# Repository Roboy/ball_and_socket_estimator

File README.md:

# Neural network ball socket estimator

## Install

* Pytorch `conda install pytorch torchvision torchaudio cudatoolkit=10.2 -c pytorch`

* `pip install -r requirements.txt`

## Data collection

Switch to `python` folder as your working directory `cd python`

* Generate data using `python particle_swarm.py --body_part BODY_PART`
  
 with `BODY_PART = {head, shoulder_left, shoulder_right, hand_left, hand_right}`

* Topics to record:

    - `/roboy/pinky/sensing/external_joint_states`
    - `/roboy/pinky/middleware/MagneticSensor`
    - `/tracking_loss`
    - `/roboy/pinky/control/cardsflow_joint_states`
    - `/roboy/pinky/simulation/joint_targets`

## Training

* Convert `bags` to `csv` using `write_dataset_from_bag.ipynb`

* Run `data_analysis.ipynb` to make sure all the inputs and outputs are correct

* Train an LSTM network using `training.ipynb`

## Prediction
`cd python`
* Run the trained network `python predict_lstm.py`

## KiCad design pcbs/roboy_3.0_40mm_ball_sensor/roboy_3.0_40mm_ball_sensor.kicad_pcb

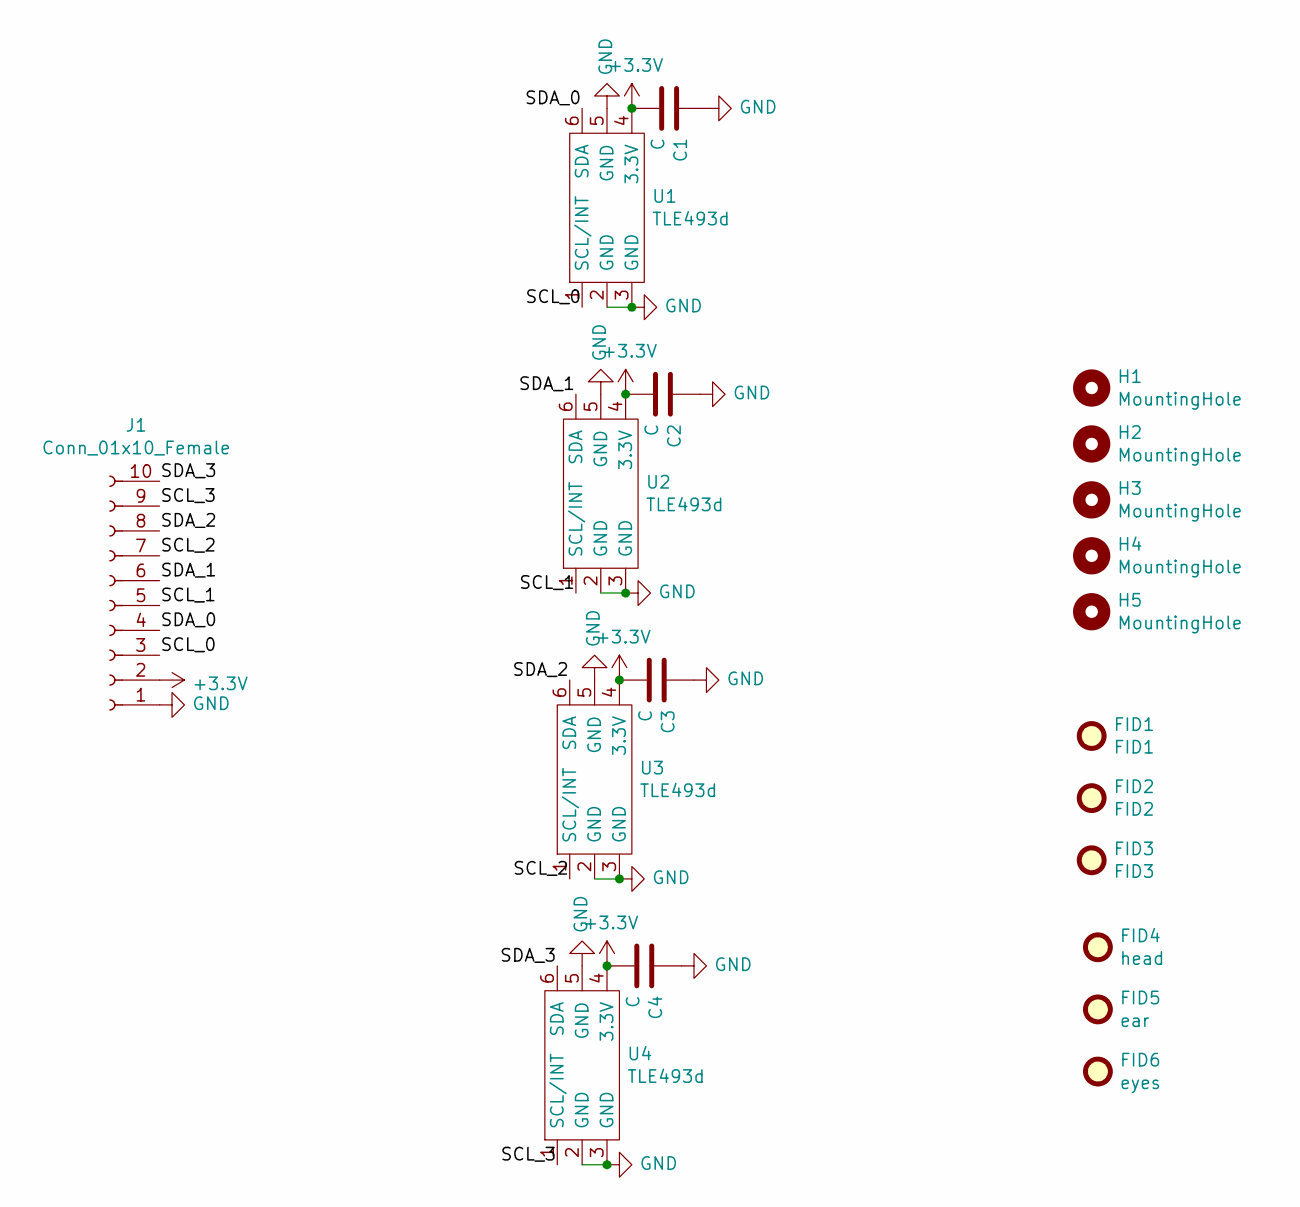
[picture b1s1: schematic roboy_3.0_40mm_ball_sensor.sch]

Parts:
C1, C2, C3, C4: C; C_0402_1005Metric
FID1: FID1; Fiducial_0.5mm_Mask1mm
FID2: FID2; Fiducial_0.5mm_Mask1mm
FID3: FID3; Fiducial_0.5mm_Mask1mm
FID4: head; R1_face_mask_5.5mm
FID5: ear; R1_ear_silk_5.5mm
FID6: eyes; R1_eyes_mask_5.5mm
H1, H2, H3, H4, H5: MountingHole; MountingHole_3.2mm_M3
J1: Conn_01x10_Female; TE-Connectivity_Micro-Match_connector_02x05_Pitch_1.27mm
U1, U2, U3, U4: TLE493d

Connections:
+3V3: C1.2, C2.2, C3.2, C4.2, J1.2, U1.4 (3.3V), U2.4 (3.3V), U3.4 (3.3V), U4.4 (3.3V)
/SCL_0: J1.3, U1.1 (SCL/INT)
/SCL_1: J1.5, U2.1 (SCL/INT)
/SCL_2: J1.7, U3.1 (SCL/INT)
/SCL_3: J1.9, U4.1 (SCL/INT)
/SDA_0: J1.4, U1.6 (SDA)
/SDA_1: J1.6, U2.6 (SDA)
/SDA_2: J1.8, U3.6 (SDA)
/SDA_3: J1.10, U4.6 (SDA)
GND: C1.1, C2.1, C3.1, C4.1, J1.1, U1.2 (GND), U1.3 (GND), U1.5 (GND), U2.2 (GND), U2.3 (GND), U2.5 (GND), U3.2 (GND), U3.3 (GND), U3.5 (GND), U4.2 (GND), U4.3 (GND), U4.5 (GND)

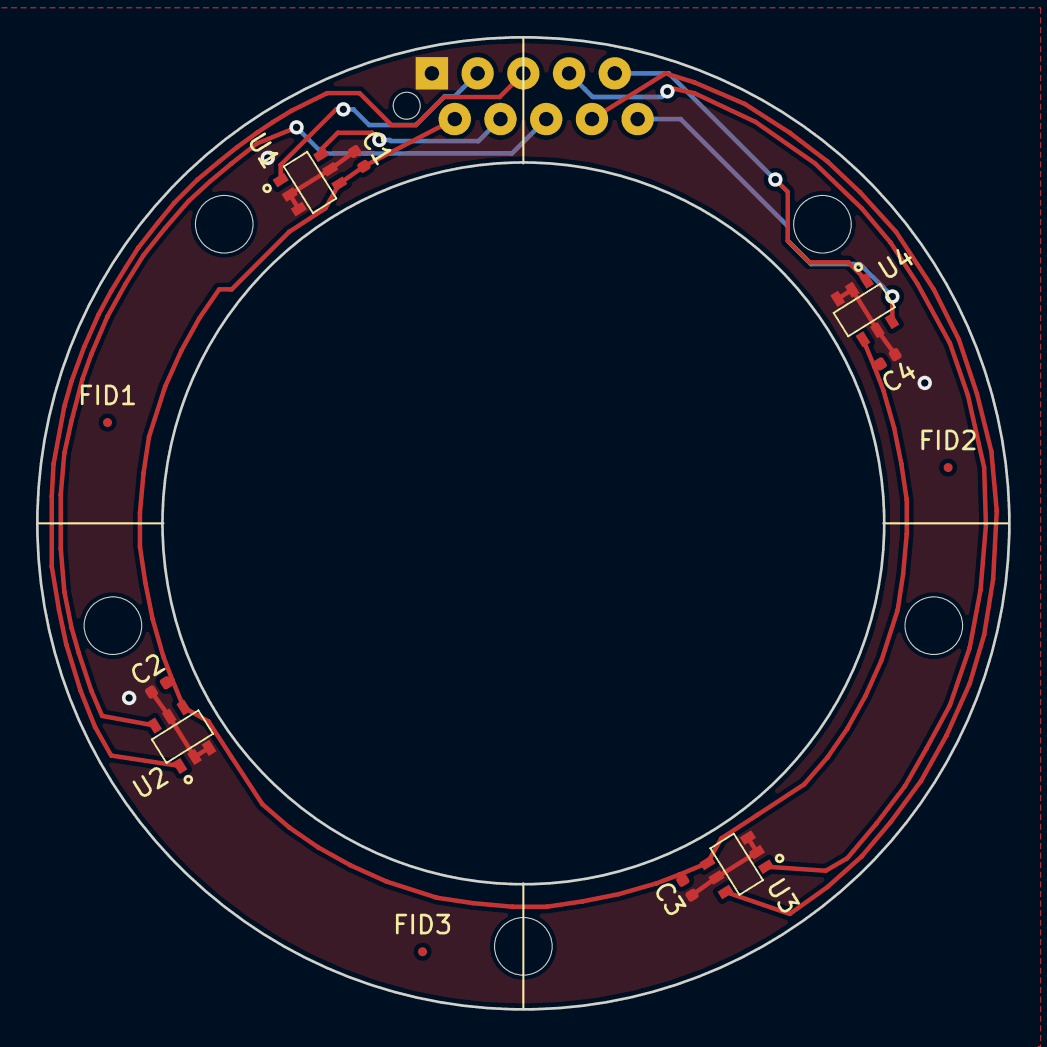
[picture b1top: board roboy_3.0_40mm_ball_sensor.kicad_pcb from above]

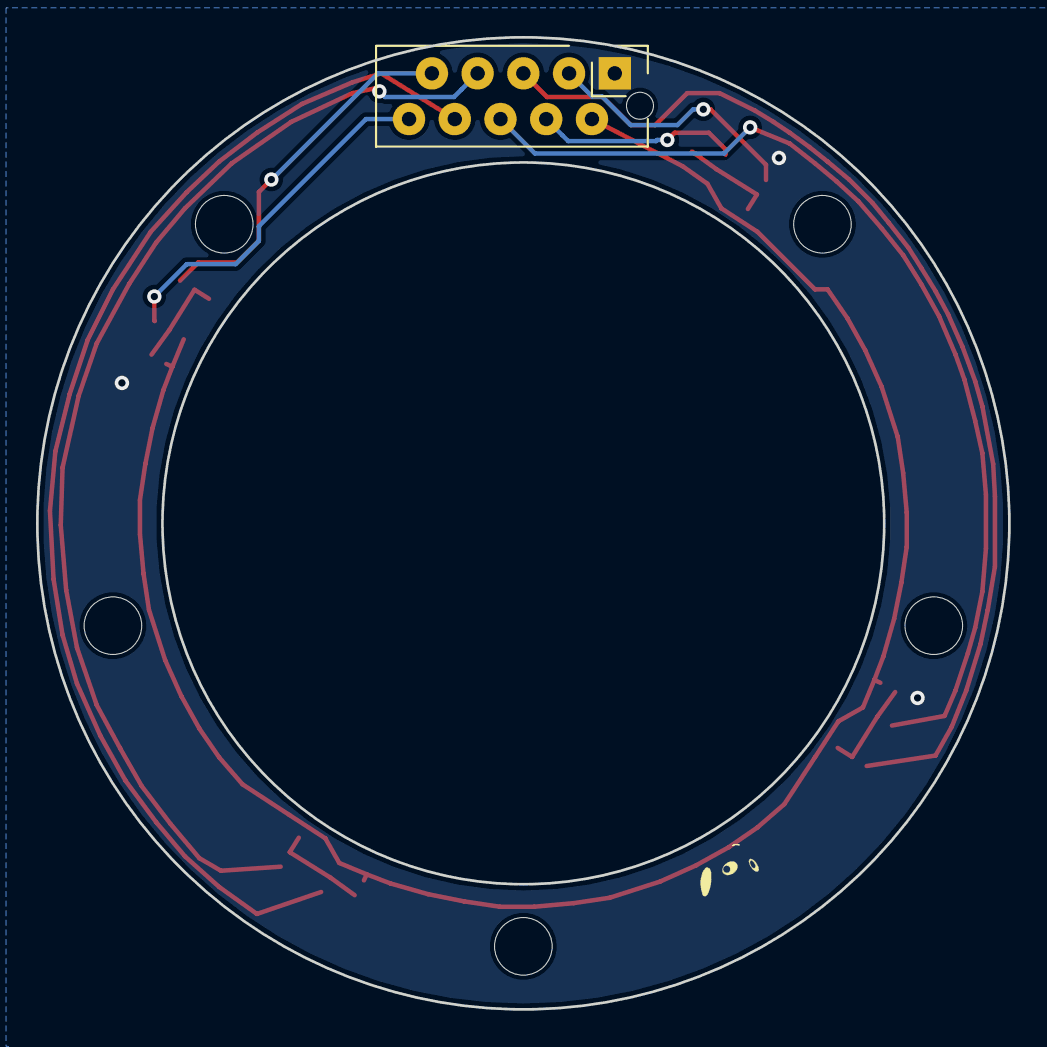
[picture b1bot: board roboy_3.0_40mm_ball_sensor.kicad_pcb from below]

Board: 2 copper layers, 54.0 x 54.0 mm, 20 parts (4 on the bottom side), 10 nets.

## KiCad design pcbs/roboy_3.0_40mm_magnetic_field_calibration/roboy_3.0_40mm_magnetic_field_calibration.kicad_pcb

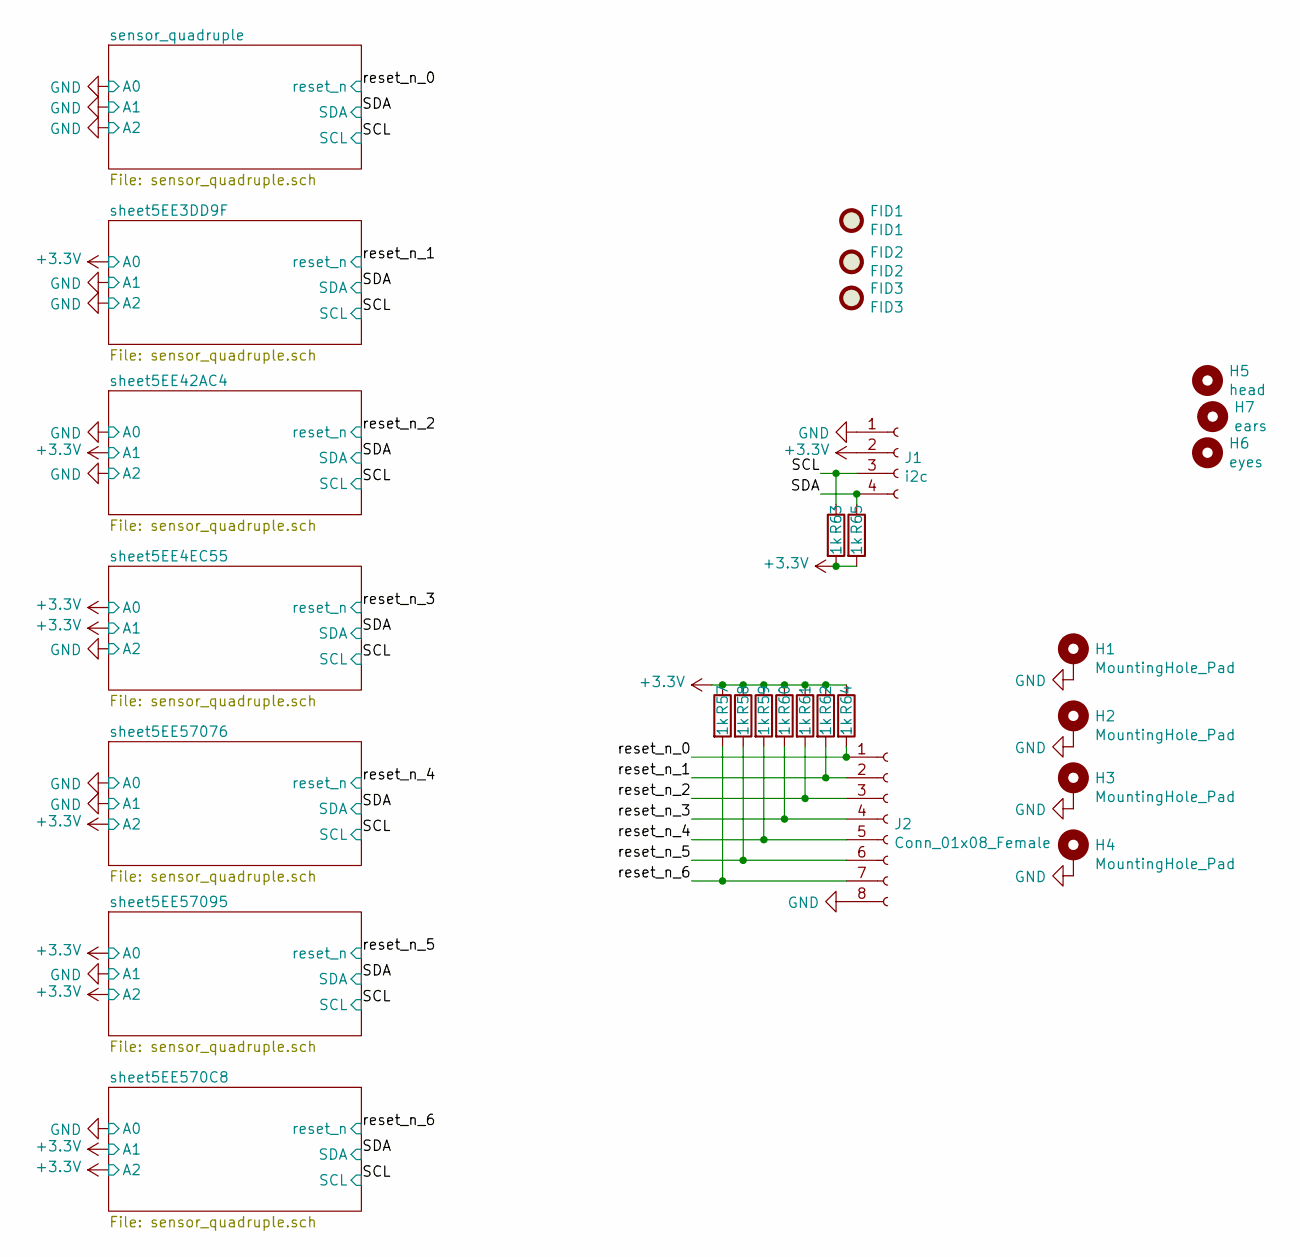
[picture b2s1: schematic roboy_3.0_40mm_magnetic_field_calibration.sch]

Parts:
FID1: FID1; Fiducial_0.75mm_Mask1.5mm
FID2: FID2; Fiducial_0.75mm_Mask1.5mm
FID3: FID3; Fiducial_0.75mm_Mask1.5mm
H1, H2, H3, H4: MountingHole_Pad; MountingHole_3mm_Pad
H5: head; R1_face_mask_5.5mm
H6: eyes; R1_eyes_mask_5.5mm
H7: ears; R1_ear_silk_5.5mm
J1: i2c; TE-Connectivity_Micro-Match_connector_02x02_Pitch_1.27mm
J2: Conn_01x08_Female; micro_match_female_8pos_SMT
R57, R58, R59, R60, R61, R62, R63, R64, R65: 1k; R_0402_1005Metric

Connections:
+3V3: J1.2, R57.1, R58.1, R59.1, R60.1, R61.1, R62.1, R63.2, R64.1, R65.2; also elsewhere on the board
/SCL: J1.3, R63.1; also elsewhere on the board
/SDA: J1.4, R65.1; also elsewhere on the board
/reset_n_0: J2.1, R64.2; also elsewhere on the board
/reset_n_1: J2.2, R62.2; also elsewhere on the board
/reset_n_2: J2.3, R61.2; also elsewhere on the board
/reset_n_3: J2.4, R60.2; also elsewhere on the board
/reset_n_4: J2.5, R59.2; also elsewhere on the board
/reset_n_5: J2.6, R58.2; also elsewhere on the board
/reset_n_6: J2.7, R57.2; also elsewhere on the board
GND: H1.1, H2.1, H3.1, H4.1, J1.1, J2.8; also elsewhere on the board

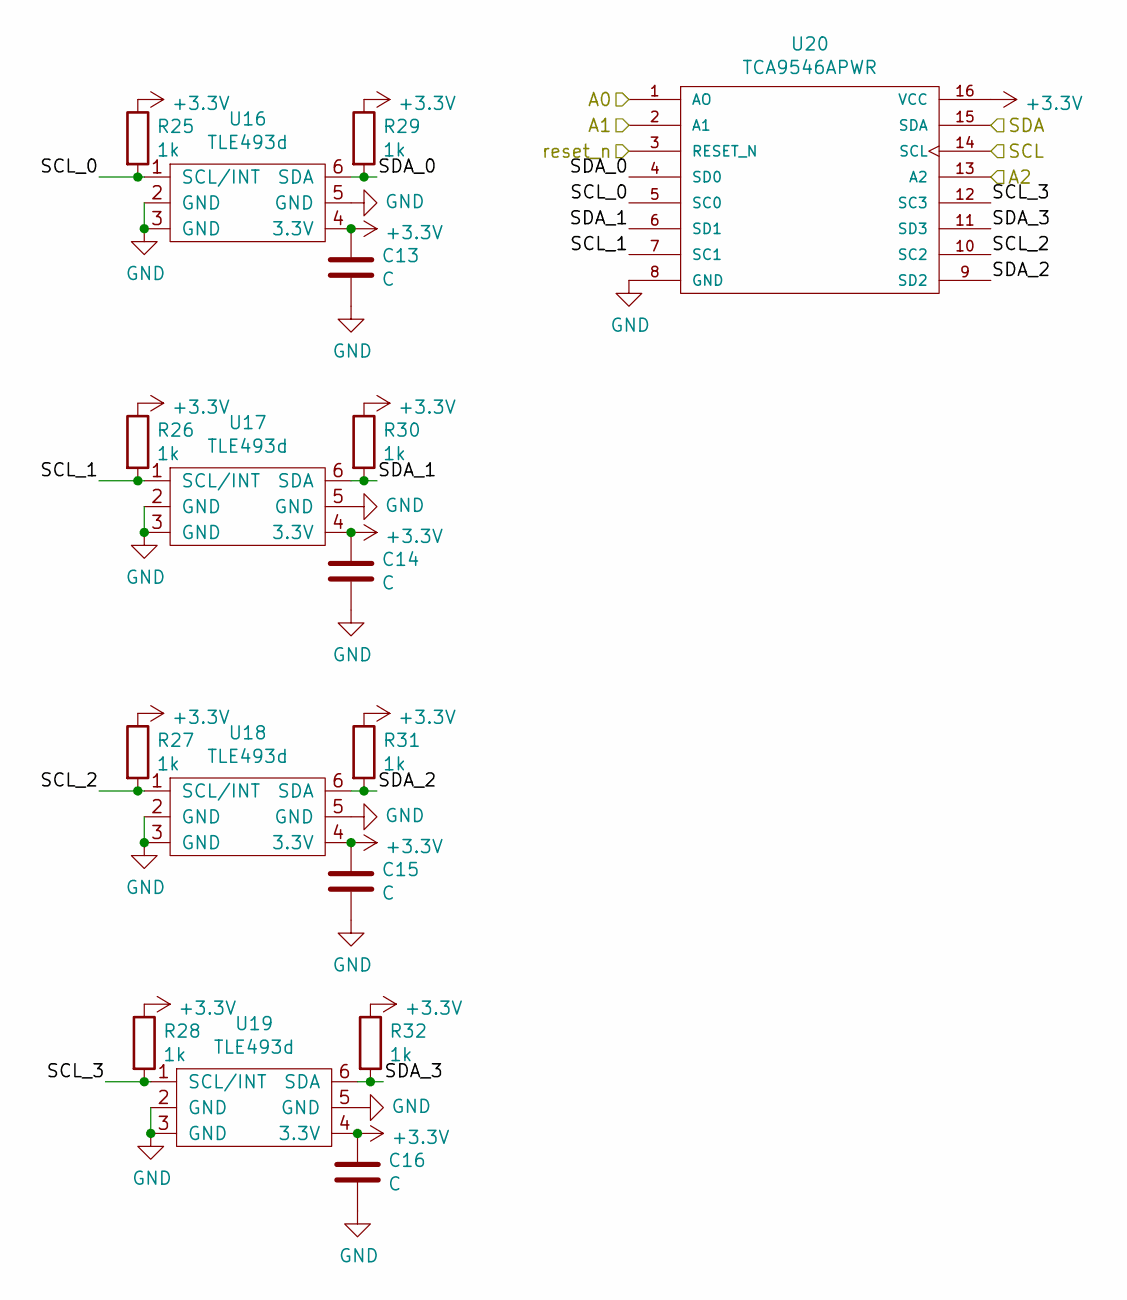
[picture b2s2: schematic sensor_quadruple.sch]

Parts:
C1, C2, C3, C4: C; C_0402_1005Metric
R1, R2, R3, R4, R5, R6, R7, R8: 1k; R_0402_1005Metric
U1, U2, U3, U4: TLE493d
U5: TCA9546APWR; SOP65P640X120-16N

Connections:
+3V3: C1.1, C2.1, C3.1, C4.1, R1.1, R2.1, R3.1, R4.1, R5.1, R6.1, R7.1, R8.1, U1.4 (3.3V), U2.4 (3.3V), U3.4 (3.3V), U4.4 (3.3V), U5.16 (VCC); also elsewhere on the board
/SCL: U5.14 (SCL); also elsewhere on the board
/SDA: U5.15 (SDA); also elsewhere on the board
/reset_n_0: U5.3 (RESET_N); also elsewhere on the board
/sensor_quadruple/SCL_0: R1.2, U1.1 (SCL/INT), U5.5 (SC0)
/sensor_quadruple/SCL_1: R2.2, U2.1 (SCL/INT), U5.7 (SC1)
/sensor_quadruple/SCL_2: R3.2, U3.1 (SCL/INT), U5.10 (SC2)
/sensor_quadruple/SCL_3: R4.2, U4.1 (SCL/INT), U5.12 (SC3)
/sensor_quadruple/SDA_0: R5.2, U1.6 (SDA), U5.4 (SD0)
/sensor_quadruple/SDA_1: R6.2, U2.6 (SDA), U5.6 (SD1)
/sensor_quadruple/SDA_2: R7.2, U3.6 (SDA), U5.9 (SD2)
/sensor_quadruple/SDA_3: R8.2, U4.6 (SDA), U5.11 (SD3)
GND: C1.2, C2.2, C3.2, C4.2, U1.2 (GND), U1.3 (GND), U1.5 (GND), U2.2 (GND), U2.3 (GND), U2.5 (GND), U3.2 (GND), U3.3 (GND), U3.5 (GND), U4.2 (GND), U4.3 (GND), U4.5 (GND), U5.1 (AO), U5.2 (A1), U5.8 (GND), U5.13 (A2); also elsewhere on the board

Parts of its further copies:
C5, C6, C7, C8, C9, C10, C11, C12, C13, C14, C15, C16, C17, C18, C19, C20, C21, C22, C23, C24, C25, C26, C27, C28: C; C_0402_1005Metric
R9, R10, R11, R12, R13, R14, R15, R16, R17, R18, R19, R20, R21, R22, R23, R24, R25, R26, R27, R28, R29, R30, R31, R32, R33, R34, R35, R36, R37, R38, R39, R40, R41, R42, R43, R44, R45, R46, R47, R48, R49, R50, R51, R52, R53, R54, R55, R56: 1k; R_0402_1005Metric
U6, U7, U8, U9, U11, U12, U13, U14, U16, U17, U18, U19, U21, U22, U23, U24, U26, U27, U28, U29, U31, U32, U33, U34: TLE493d
U10, U15, U20, U25, U30, U35: TCA9546APWR; SOP65P640X120-16N

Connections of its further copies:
+3V3: C5.1, C6.1, C7.1, C8.1, C9.1, C10.1, C11.1, C12.1, C13.1, C14.1, C17.1, C18.1, C19.1, C20.1, C21.1, C22.1, C23.1, C24.1, C25.1, C26.1, C27.1, C28.1, R9.1, R10.1, R11.1, R12.1, R13.1, R14.1, R15.1, R16.1, R17.1, R18.1, R19.1, R20.1, R21.1, R22.1, R23.1, R24.1, R25.1, R26.1, R29.1, R30.1, R33.1, R34.1, R35.1, R36.1, R37.1, R38.1, R39.1, R40.1, R41.1, R42.1, R43.1, R44.1, R45.1, R46.1, R47.1, R48.1, R49.1, R50.1, R51.1, R52.1, R53.1, R54.1, R55.1, R56.1, U6.4 (3.3V), U7.4 (3.3V), U8.4 (3.3V), U9.4 (3.3V), U10.1 (AO), U10.16 (VCC), U11.4 (3.3V), U12.4 (3.3V), U13.4 (3.3V), U14.4 (3.3V), U15.2 (A1), U15.16 (VCC), U16.4 (3.3V), U17.4 (3.3V), U20.1 (AO), U20.2 (A1), U20.16 (VCC), U21.4 (3.3V), U22.4 (3.3V), U23.4 (3.3V), U24.4 (3.3V), U25.13 (A2), U25.16 (VCC), U26.4 (3.3V), U27.4 (3.3V), U28.4 (3.3V), U29.4 (3.3V), U30.1 (AO), U30.13 (A2), U30.16 (VCC), U31.4 (3.3V), U32.4 (3.3V), U33.4 (3.3V), U34.4 (3.3V), U35.2 (A1), U35.13 (A2), U35.16 (VCC); also elsewhere on the board
/SCL: U10.14 (SCL), U15.14 (SCL), U20.14 (SCL), U25.14 (SCL), U30.14 (SCL), U35.14 (SCL); also elsewhere on the board
/SDA: U10.15 (SDA), U15.15 (SDA), U20.15 (SDA), U25.15 (SDA), U30.15 (SDA), U35.15 (SDA); also elsewhere on the board
/reset_n_1: U10.3 (RESET_N); also elsewhere on the board
/reset_n_2: U15.3 (RESET_N); also elsewhere on the board
/reset_n_3: U20.3 (RESET_N); also elsewhere on the board
/reset_n_4: U25.3 (RESET_N); also elsewhere on the board
/reset_n_5: U30.3 (RESET_N); also elsewhere on the board
/reset_n_6: U35.3 (RESET_N); also elsewhere on the board
/sheet5EE3DD9F/SCL_0: R9.2, U6.1 (SCL/INT), U10.5 (SC0)
/sheet5EE3DD9F/SCL_1: R10.2, U7.1 (SCL/INT), U10.7 (SC1)
/sheet5EE3DD9F/SCL_2: R11.2, U8.1 (SCL/INT), U10.10 (SC2)
/sheet5EE3DD9F/SCL_3: R12.2, U9.1 (SCL/INT), U10.12 (SC3)
/sheet5EE3DD9F/SDA_0: R13.2, U6.6 (SDA), U10.4 (SD0)
/sheet5EE3DD9F/SDA_1: R14.2, U7.6 (SDA), U10.6 (SD1)
/sheet5EE3DD9F/SDA_2: R15.2, U8.6 (SDA), U10.9 (SD2)
/sheet5EE3DD9F/SDA_3: R16.2, U9.6 (SDA), U10.11 (SD3)
/sheet5EE4EC55/SCL_0: R25.2, U16.1 (SCL/INT), U20.5 (SC0)
/sheet5EE4EC55/SCL_1: R26.2, U17.1 (SCL/INT), U20.7 (SC1)
/sheet5EE4EC55/SCL_2: U20.10 (SC2)
/sheet5EE4EC55/SCL_3: U20.12 (SC3)
/sheet5EE4EC55/SDA_0: R29.2, U16.6 (SDA), U20.4 (SD0)
/sheet5EE4EC55/SDA_1: R30.2, U17.6 (SDA), U20.6 (SD1)
/sheet5EE4EC55/SDA_2: U20.9 (SD2)
/sheet5EE4EC55/SDA_3: U20.11 (SD3)
/sheet5EE42AC4/SCL_0: R17.2, U11.1 (SCL/INT), U15.5 (SC0)
/sheet5EE42AC4/SCL_1: R18.2, U12.1 (SCL/INT), U15.7 (SC1)
/sheet5EE42AC4/SCL_2: R19.2, U13.1 (SCL/INT), U15.10 (SC2)
/sheet5EE42AC4/SCL_3: R20.2, U14.1 (SCL/INT), U15.12 (SC3)
/sheet5EE42AC4/SDA_0: R21.2, U11.6 (SDA), U15.4 (SD0)
/sheet5EE42AC4/SDA_1: R22.2, U12.6 (SDA), U15.6 (SD1)
/sheet5EE42AC4/SDA_2: R23.2, U13.6 (SDA), U15.9 (SD2)
/sheet5EE42AC4/SDA_3: R24.2, U14.6 (SDA), U15.11 (SD3)
/sheet5EE570C8/SCL_0: R49.2, U31.1 (SCL/INT), U35.5 (SC0)
/sheet5EE570C8/SCL_1: R50.2, U32.1 (SCL/INT), U35.7 (SC1)
/sheet5EE570C8/SCL_2: R51.2, U33.1 (SCL/INT), U35.10 (SC2)
/sheet5EE570C8/SCL_3: R52.2, U34.1 (SCL/INT), U35.12 (SC3)
/sheet5EE570C8/SDA_0: R53.2, U31.6 (SDA), U35.4 (SD0)
/sheet5EE570C8/SDA_1: R54.2, U32.6 (SDA), U35.6 (SD1)
/sheet5EE570C8/SDA_2: R55.2, U33.6 (SDA), U35.9 (SD2)
/sheet5EE570C8/SDA_3: R56.2, U34.6 (SDA), U35.11 (SD3)
/sheet5EE57076/SCL_0: R33.2, U21.1 (SCL/INT), U25.5 (SC0)
/sheet5EE57076/SCL_1: R34.2, U22.1 (SCL/INT), U25.7 (SC1)
/sheet5EE57076/SCL_2: R35.2, U23.1 (SCL/INT), U25.10 (SC2)
/sheet5EE57076/SCL_3: R36.2, U24.1 (SCL/INT), U25.12 (SC3)
/sheet5EE57076/SDA_0: R37.2, U21.6 (SDA), U25.4 (SD0)
/sheet5EE57076/SDA_1: R38.2, U22.6 (SDA), U25.6 (SD1)
/sheet5EE57076/SDA_2: R39.2, U23.6 (SDA), U25.9 (SD2)
/sheet5EE57076/SDA_3: R40.2, U24.6 (SDA), U25.11 (SD3)
/sheet5EE57095/SCL_0: R41.2, U26.1 (SCL/INT), U30.5 (SC0)
/sheet5EE57095/SCL_1: R42.2, U27.1 (SCL/INT), U30.7 (SC1)
/sheet5EE57095/SCL_2: R43.2, U28.1 (SCL/INT), U30.10 (SC2)
/sheet5EE57095/SCL_3: R44.2, U29.1 (SCL/INT), U30.12 (SC3)
/sheet5EE57095/SDA_0: R45.2, U26.6 (SDA), U30.4 (SD0)
/sheet5EE57095/SDA_1: R46.2, U27.6 (SDA), U30.6 (SD1)
/sheet5EE57095/SDA_2: R47.2, U28.6 (SDA), U30.9 (SD2)
/sheet5EE57095/SDA_3: R48.2, U29.6 (SDA), U30.11 (SD3)
GND: C5.2, C6.2, C7.2, C8.2, C9.2, C10.2, C11.2, C12.2, C13.2, C14.2, C17.2, C18.2, C19.2, C20.2, C21.2, C22.2, C23.2, C24.2, C25.2, C26.2, C27.2, C28.2, U6.2 (GND), U6.3 (GND), U6.5 (GND), U7.2 (GND), U7.3 (GND), U7.5 (GND), U8.2 (GND), U8.3 (GND), U8.5 (GND), U9.2 (GND), U9.3 (GND), U9.5 (GND), U10.2 (A1), U10.8 (GND), U10.13 (A2), U11.2 (GND), U11.3 (GND), U11.5 (GND), U12.2 (GND), U12.3 (GND), U12.5 (GND), U13.2 (GND), U13.3 (GND), U13.5 (GND), U14.2 (GND), U14.3 (GND), U14.5 (GND), U15.1 (AO), U15.8 (GND), U15.13 (A2), U16.2 (GND), U16.3 (GND), U16.5 (GND), U17.2 (GND), U17.3 (GND), U17.5 (GND), U20.8 (GND), U20.13 (A2), U21.2 (GND), U21.3 (GND), U21.5 (GND), U22.2 (GND), U22.3 (GND), U22.5 (GND), U23.2 (GND), U23.3 (GND), U23.5 (GND), U24.2 (GND), U24.3 (GND), U24.5 (GND), U25.1 (AO), U25.2 (A1), U25.8 (GND), U26.2 (GND), U26.3 (GND), U26.5 (GND), U27.2 (GND), U27.3 (GND), U27.5 (GND), U28.2 (GND), U28.3 (GND), U28.5 (GND), U29.2 (GND), U29.3 (GND), U29.5 (GND), U30.2 (A1), U30.8 (GND), U31.2 (GND), U31.3 (GND), U31.5 (GND), U32.2 (GND), U32.3 (GND), U32.5 (GND), U33.2 (GND), U33.3 (GND), U33.5 (GND), U34.2 (GND), U34.3 (GND), U34.5 (GND), U35.1 (AO), U35.8 (GND); also elsewhere on the board

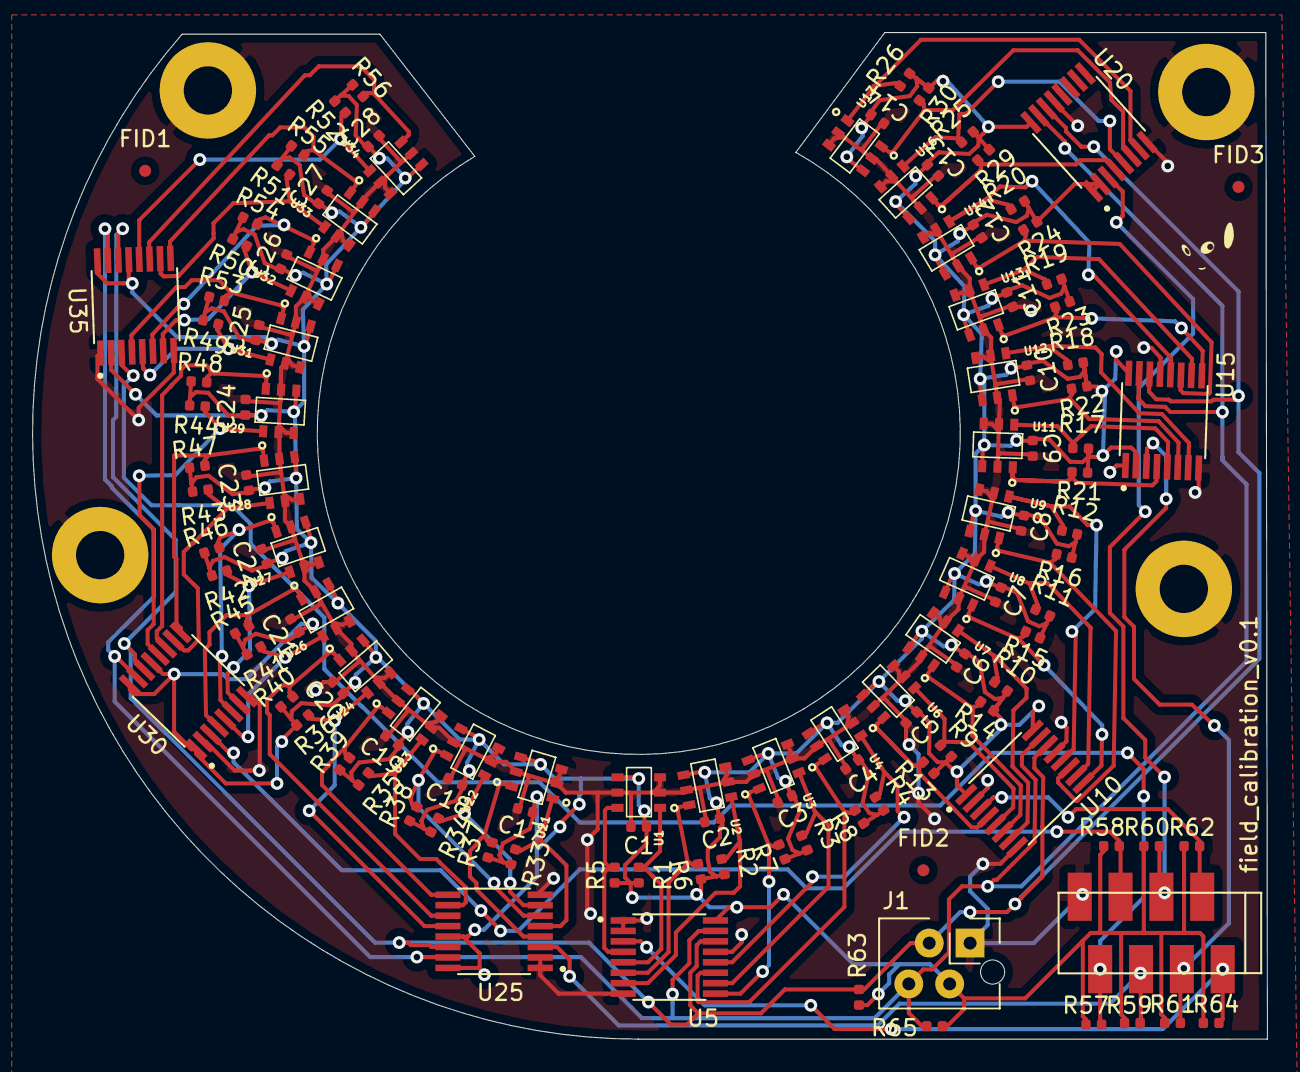
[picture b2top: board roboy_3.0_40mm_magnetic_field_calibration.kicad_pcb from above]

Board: 2 copper layers, 76.8 x 62.6 mm, 132 parts (0 on the bottom side), 63 nets.

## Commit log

2017-06-09 uh babay!
2017-06-10 with draft neural net
2017-06-10 works with neural net trained on real data
2018-02-27 with optional recording before training
2018-10-01 removed some trash
2018-10-02 with sigmoid
2018-10-03 bigger network
2018-10-04 with model save and load
2018-10-04 train train train
2018-10-04 quite decent result
2018-10-04 with data
2018-10-07 visualizing the magnetic field with point cloud library
2018-11-09 trained
2018-11-09 a bit jittery
2018-11-11 using trained network
2018-12-04 draft
2018-12-05 with simulation pose
2018-12-06 with pcl visualization
2018-12-06 ros2 refactored
2018-12-07 better
2019-01-02 with visualization
2019-01-04 fully trained for left shoulder
2019-01-06 hyperparameter search
2019-01-07 hyperparameter
2019-03-19 add pcl dependecies for ubuntu 18
2019-03-29 with training and python script for gridmap
2019-03-29 grid better
2019-03-31 adaptesd fort euler
2019-03-31 fixed replay for euler
2019-04-04 better training
2019-04-04 smoothie
2019-04-04 with predictor
2019-04-04 better grid map
2019-04-04 fix correct current euler angles
2019-04-05 hyper hyper
2019-04-06 good training
2019-04-11 better gridmap better training
2019-04-11 d minor
2019-04-11 trainied to perfection..
2019-04-12 pretty well trained
2019-05-01 shoulder_left
2019-05-02 more training
2019-05-18 use sftp option
2019-05-19 draft particle swarm
2019-05-19 particle swarm ready
2019-05-19 with connection to real platform
2019-05-19 should work
2019-08-18 ring sensor for neck
2019-08-19 layout finished
2019-08-20 bigger ring
2019-08-21 adapted to train different body parts
2019-09-05 leia status
2019-09-23 ordered on pcbway
2019-09-24 leia status finals
2020-01-17 preliminary training, error below 1 degree
2020-01-18 fixed hyperparameter search, visualization with robot model
2020-01-18 beschde neck
2020-01-21 with grid map
2020-02-05 for shoulder
2020-02-05 shoulder_right trained
2020-02-12 shoulder_left trained
2020-02-12 no hardcoded path from letrend
2020-02-12 with runningmean
2020-03-26 writing to video
2020-03-27 with 3d animation
2020-03-27 with offscreen rendering
2020-03-28 tetrahedron
2020-03-28 better boundaries
2020-03-30 all in one video
2020-03-31 hallbach
2020-04-02 actual pose estimation using real sensor data
2020-04-02 brute force tries...
2020-04-08 removed old rubbisch
2020-04-28 with parallel training data generation
2020-05-05 with wrist_left and head trained
2020-05-14 shoulder_left with locked joint
2020-05-19 inverted magnets
2020-05-19 abort!
2020-05-19 180 degress rotated
2020-05-19 again
2020-05-22 6dof calibration
2020-05-24 with sim data generator and ball config in calibration
2020-05-24 finds simulated calibration values
2020-05-25 with real sensor value logger
2020-05-25 with cleaner magneticfieldcalibration class
2020-05-25 fixed sensor logger
2020-05-25 sensor selector
2020-05-26 with sensor merge and printout
2020-05-26 with pose estimator uo to track
2020-05-27 two magnets arrangement giving decent results
2020-05-27 magnetic field collision
2020-05-27 magnetic collision multiprocessing
2020-05-28 magjointlib
2020-05-28 three stages
2020-05-29 with magent arrangement optimizer draft
2020-05-29 with calibration
2020-05-29 using all data for training, d'oh
2020-05-29 bigger joint space
2020-05-30 particle swarm
2020-05-31 more arrangements
2020-05-31 with getDP magnetic field simulation
2020-06-01 with pycuda collision calculation
2020-06-02 with particel swarm using cuda for collisions
2020-06-03 magnetic field visualization
2020-06-03 more configs
2020-06-05 with texture memory for magnetic field interpolation
2020-06-05 with full sphere and normalized coordinates
2020-06-05 with actual magnetic field data interpolation
2020-06-05 with spherical coordinate calculation in kernel
2020-06-05 full angle range
2020-06-06 with poseestimator using texture memory cuda
2020-06-06 argparse
2020-06-06 with field calibration pcb
2020-06-06 ordered on aisler
2020-06-07 with 3d model
2020-06-09 sensors on circle
2020-06-09 with sensors on circle
2020-06-11 draft trilinear
2020-06-23 with magnetic field calibration draft
2020-06-24 with correct sensor alignment
2020-06-24 with sensor select
2020-06-24 invert sensor values on opposite pcb side
2020-06-24 with loading npz in c++ and spherical coordinates
2020-06-24 quantize half the sphere
2020-06-25 more more more
2020-06-26 mapping to spherical coordinates correct
2020-06-26 with crude interpolation
2020-06-28 draft pose estimator
2020-06-29 hm minimizer not working yet
2020-06-30 with interpolation in python
2020-07-01 with estimator on real sensor data
2020-07-01 the sensors are not aligned properly for some reason, but using one half of the pcb gives preliminary good position estimates
2020-07-03 trying to align
2020-07-06 with ball joint sensor config
2020-07-07 with clearer coordinate system
2020-07-08 clean up a bit and bisec_left method for getting closest value
2020-07-08 trying to come up with a better interpolation function
2020-07-09 with almost correct interpolation using pycuda and real sensor data
2020-07-09 trying pose estimation
2020-07-10 ah that makes more sense
2020-07-10 transforms seem correct
2020-07-10 using sensor config
2020-07-12 hm what is global now?
2020-07-14 cooridnate transforms...
2020-08-18 nuc latest
2020-09-08 tmp build for jetson
2021-04-06 c++14
2021-05-26 Magnetic sensors to Euler Angles via Neural Network
2021-05-26 Updated network
2021-05-28 Updated with multiple networks
2021-06-01 Rename file to predict and remove the training data
2021-06-01 Rename topic
2021-06-02 Left shoulder model
2021-06-15 Left shoulder model update with README
2021-07-14 Adding moving average filter to remove outliers
2021-07-23 Auto reset after rejecting 10 abnormal values
2021-08-06 Added LSTM model
2021-08-13 Ready for XPrize Semi-final
2021-08-17 less history for lstm, rejecting on single axis diff base
2021-08-24 Resolve comments
2021-08-24 Fixed typo
2022-01-31 Add DVBF
2022-02-08 Bag to csv
2022-02-11 DVBF and LSTM live evaluation
2022-02-14 Update predict comparison
2022-02-14 Update libs for prediction
2022-02-15 Partly fixed the memory leak for DVBF prediction
2022-02-15 Update write_data
2022-02-15 Updated LSTM
2022-02-15 Update folder
2022-02-15 Updated predict_lstm
2022-03-01 ready to test on nano
2022-03-03 DVBFs tested on left shoulder
2022-03-03 Ignore the output network for now
2022-03-03 Tested DVBFs
2022-04-02 Final result
2022-04-17 Update regularisation term for dvbf and outside validation set
2022-04-25 Latest training results with fast_data
2022-05-04 Update networks
2022-07-07 removed legacy python code, move readme to root
2022-07-07 Bump tensorflow from 2.5.0 to 2.7.2 in /python
    Bumps [tensorflow](https://github.com/tensorflow/tensorflow) from 2.5.0 to 2.7.2.
    - [Release notes](https://github.com/tensorflow/tensorflow/releases)
    - [Changelog](https://github.com/tensorflow/tensorflow/blob/master/RELEASE.md)
    - [Commits](https://github.com/tensorflow/tensorflow/compare/v2.5.0...v2.7.2)
    ---
    updated-dependencies:
2022-07-20 satisfying shoulder left model trained
